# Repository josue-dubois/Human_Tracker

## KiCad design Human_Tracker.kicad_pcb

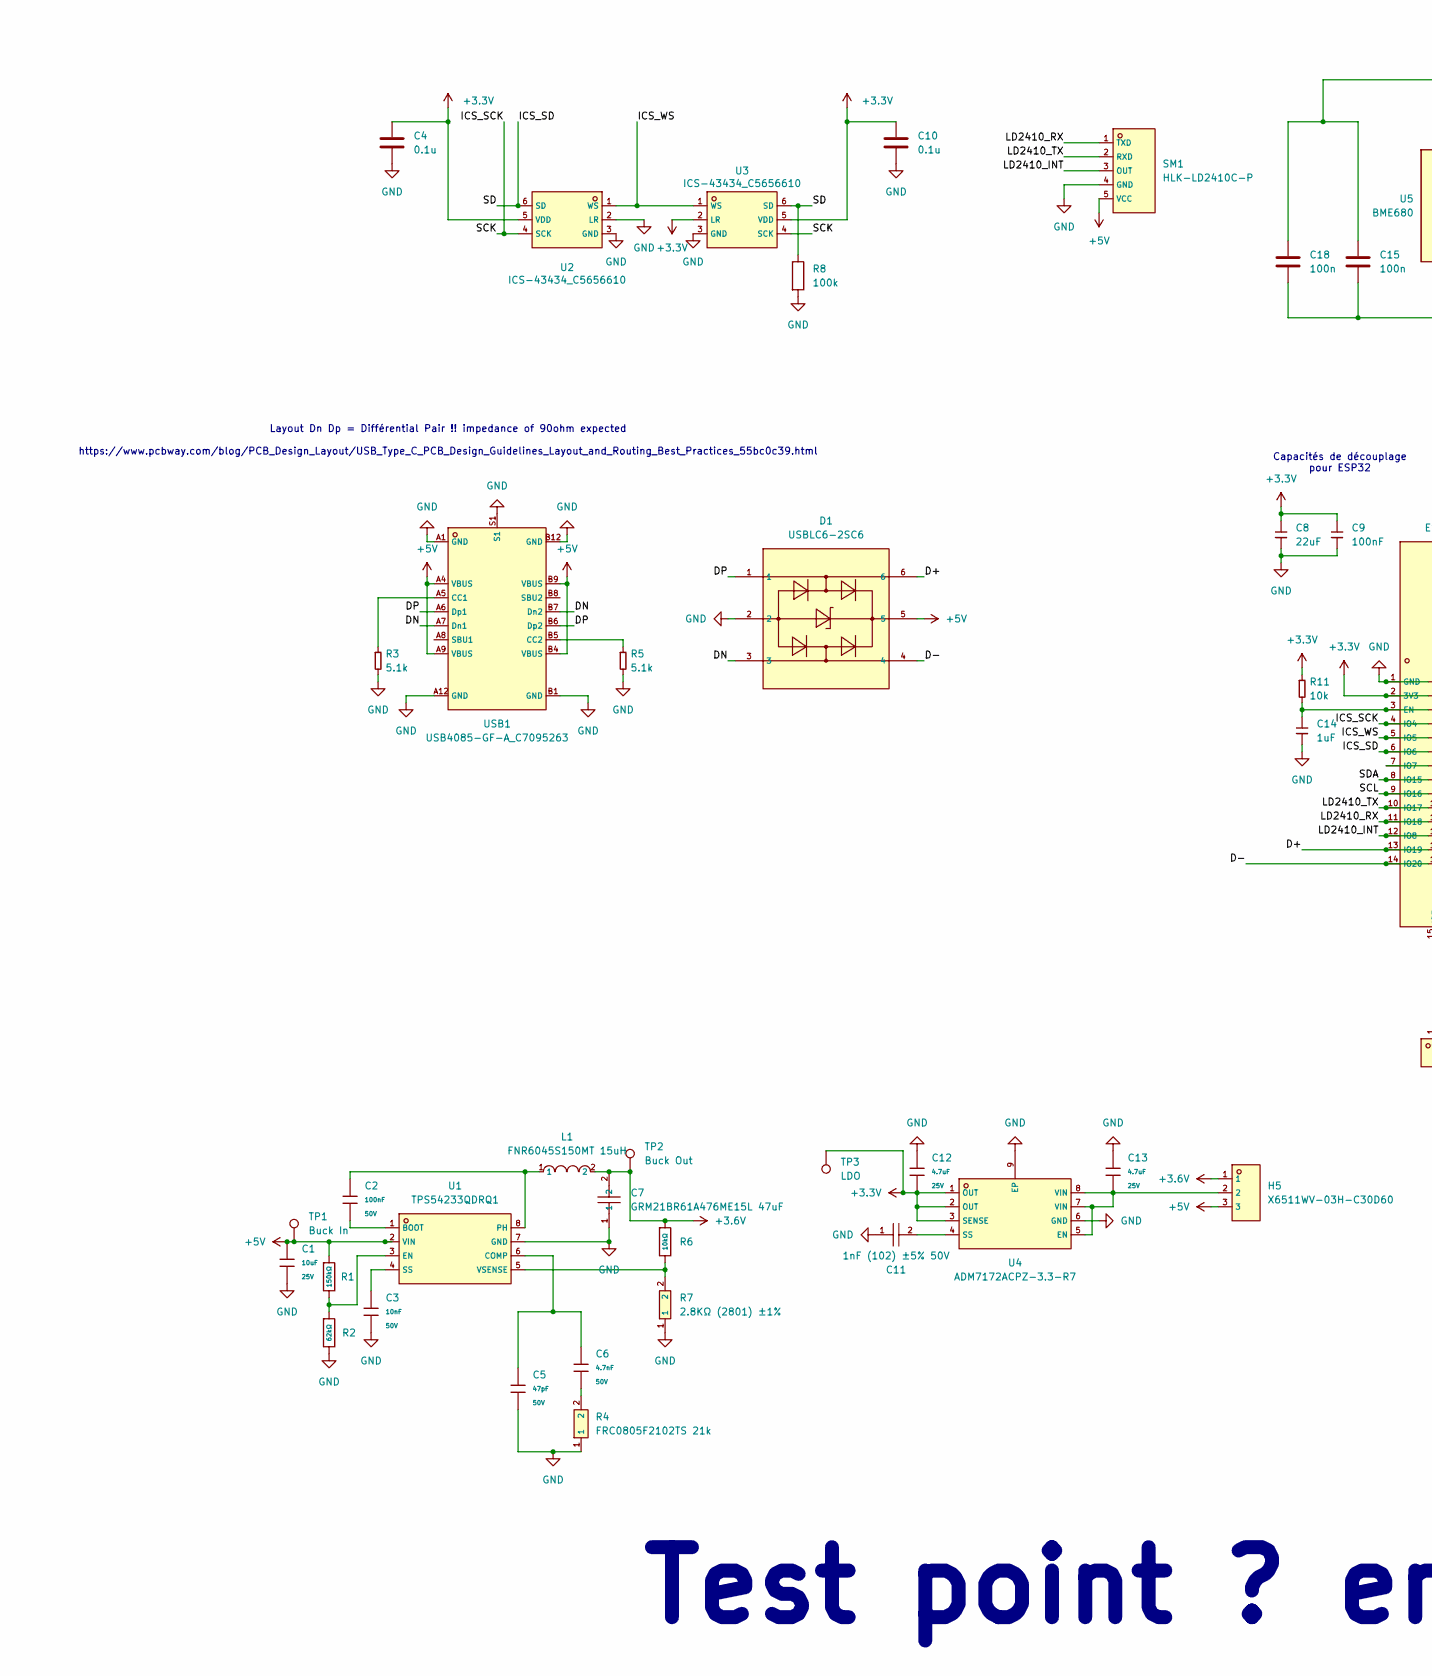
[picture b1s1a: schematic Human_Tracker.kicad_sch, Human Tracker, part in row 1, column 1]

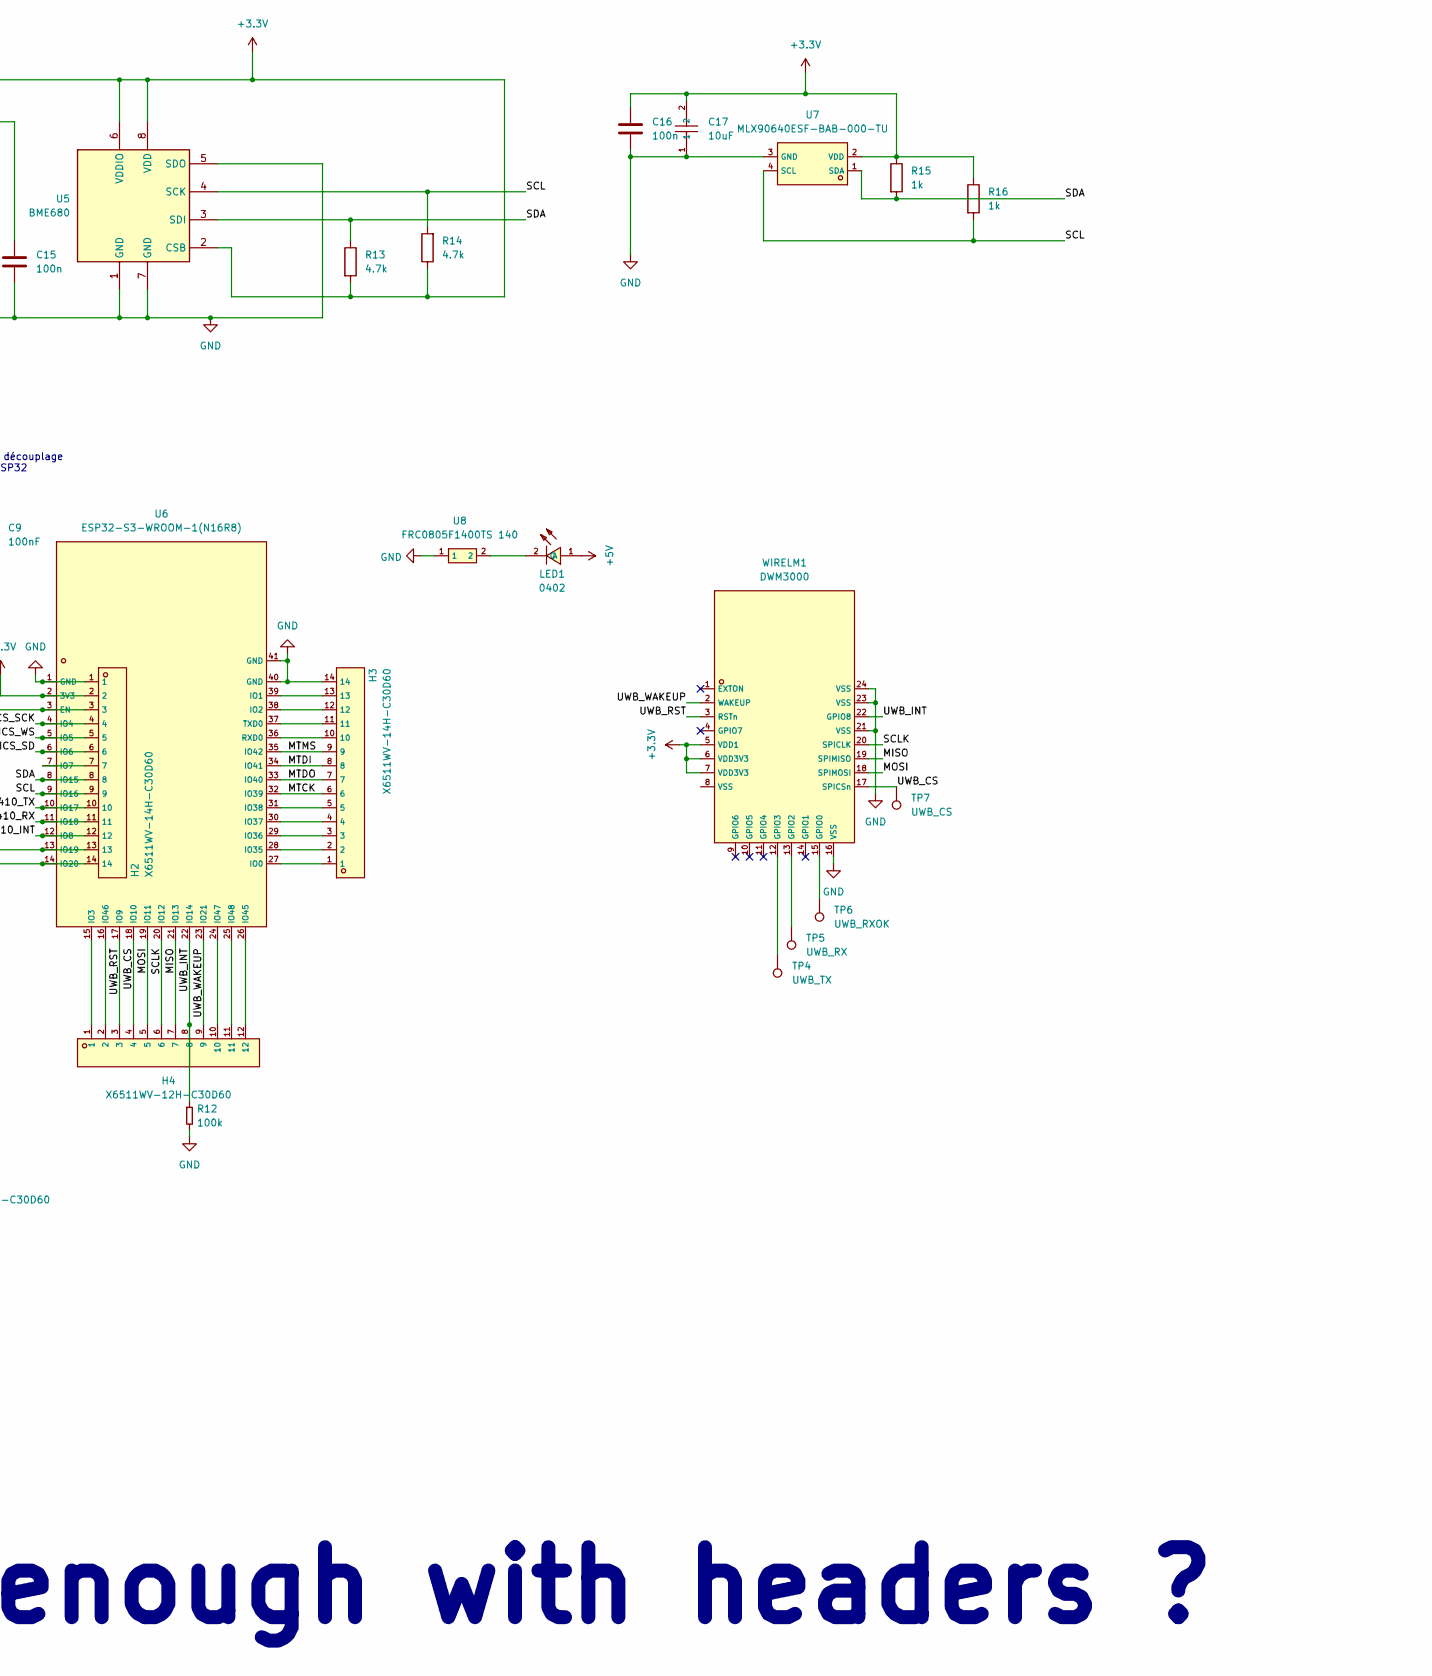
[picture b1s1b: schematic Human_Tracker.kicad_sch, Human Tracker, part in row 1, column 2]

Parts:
C1: 10uF; C1712_C0805; Voltage Rated 25V; Tolerance ±10%; Part CL21A106KAYNNNE; LCSC C15850
C2: 100nF; C1712_C0805; Voltage Rated 50V; Tolerance ±10%; Part CC0805KRX7R9BB104; LCSC C49678
C3: 10nF; C1712_C0805; Voltage Rated 50V; Tolerance ±10%; Part CL21B103KBANNNC; LCSC C1710
C4, C10: 0.1u; C1712_C0805
C5: 47pF; C1712_C0805; Voltage Rated 50V; Tolerance ±5%; Part CL21C470JBANNNC; LCSC C14857
C6: 4.7nF; C1712_C0805; Voltage Rated 50V; Tolerance ±10%; Part 0805B472K500NT; LCSC C1744
C7: GRM21BR61A476ME15L 47uF; C1712_C0805; LCSC C124129
C8: 22uF; C1712_C0805; LCSC C29277
C9: 100nF; C1712_C0805; LCSC C49678
C11: 1nF (102) ±5% 50V; C1712_C0805; LCSC C1791
C12, C13: 4.7uF; C1712_C0805; Voltage Rated 25V; Tolerance ±10%; Part CL21A475KAQNNNE; LCSC C1779
C14: 1uF; C1712_C0805; LCSC C1712
C15, C16, C18: 100n; C1712_C0805
C17: 10uF; C15850_C0805; LCSC C15850
D1: USBLC6-2SC6; C7519_SOT-23-6_L2_9-W1_6-P0_95-LS2_8-BL; LCSC C7519
H2, H3: X6511WV-14H-C30D60; C725946_HDR-TH_14P-P2_54-V-M; LCSC C725946
H4: X6511WV-12H-C30D60; C725944_HDR-TH_12P-P2_54-V-M; LCSC C725944
H5: X6511WV-03H-C30D60; C706875_HDR-TH_3P-P2_54-V-M; LCSC C706875
L1: FNR6045S150MT 15uH; C168078_IND-SMD_L6_0-W6_0_FNR60XXS; LCSC C168078
LED1: 0402; C74338_LED0402-R-RD; LCSC C74338
R1: 150kΩ; C17414_R0805; Overload Voltage (Max) 150V; Tolerance ±1%; Part 0805W8F1503T5E; LCSC C17470
R2: 62kΩ; C17414_R0805; Overload Voltage (Max) 150V; Tolerance ±1%; Part 0805W8F6202T5E; LCSC C17783
R3, R5: 5.1k; C17414_R0805; LCSC C26023
R4: FRC0805F2102TS 21k; C17414_R0805; LCSC C2933366
R6: 10kΩ; C17414_R0805; Overload Voltage (Max) 150V; Tolerance ±1%; Part 0805W8F1002T5E; LCSC C17414
R7: 2.8KΩ (2801) ±1%; C17414_R0805; LCSC C17534
R8, R12: 100k; C17414_R0805; LCSC C25611
R11: 10k; C17414_R0805; LCSC C17414
R13, R14: 4.7k; C17414_R0805
R15, R16: 1k; C17414_R0805
SM1: HLK-LD2410C-P; C19723500_SENSOR-TH_HLK-LD2410C-P; LCSC C19723500
TP1: Buck In; TestPoint_Pad_D2.0mm
TP2: Buck Out; TestPoint_Pad_D2.0mm
TP3: LDO; TestPoint_Pad_D2.0mm
TP4: UWB_TX; TestPoint_Pad_D2.0mm
TP5: UWB_RX; TestPoint_Pad_D2.0mm
TP6: UWB_RXOK; TestPoint_Pad_D2.0mm
TP7: UWB_CS; TestPoint_Pad_D2.0mm
U1: TPS54233QDRQ1; C2865142_SOIC-8_L4_9-W3_9-P1_27-LS6_0-BL; LCSC C2865142
U2, U3: ICS-43434_C5656610; C5656610_MIC-SMD_6P-L3_5-W2_7-P0_90-BL; LCSC C5656610
U4: ADM7172ACPZ-3.3-R7; C514342_DFN-8_L3_0-W3_0-P0_50-BL-EP; LCSC C514342
U5: BME680; Bosch_LGA-8_3x3mm_P0.8mm_ClockwisePinNumbering
U6: ESP32-S3-WROOM-1(N16R8); C2913202_WIRELM-SMD_ESP32-S3-WROOM-1; LCSC C2913202
U7: MLX90640ESF-BAB-000-TU; C488251_TO-39-4_MLX90640ESF-BAB-000-TU; LCSC C488251
U8: FRC0805F1400TS 140; C2930166_R0805; LCSC C2930166
USB1: USB4085-GF-A_C7095263; C7095263_USC-C-SMD_USB4085-GF-A; LCSC C7095263
WIRELM1: DWM3000; C3028890_WIRELM-SMD_DWM3000; LCSC C3028890

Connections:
+3.3V: C4.1, C8.1, C9.1, C10.1, C12.2, C15.1, C16.1, C17.2, C18.1, H2.2, R11.1, R13.2, R14.1, R15.1, R16.1, TP3.1 (1_1), U2.5 (VDD), U3.2 (LR), U3.5 (VDD), U4.1 (OUT), U4.2 (OUT), U4.3 (SENSE), U5.2 (CSB), U5.6 (VDDIO), U5.8 (VDD), U6.2 (3V3), U7.2 (VDD), WIRELM1.5 (VDD1), WIRELM1.6 (VDD3V3), WIRELM1.7 (VDD3V3)
+3.6V: C7.2, H5.1, L1.2, R6.1, TP2.1 (1_1)
+5V: C1.1, D1.5, H5.3, LED1.1 (A), R1.1, SM1.5 (VCC), TP1.1 (1_1), U1.2 (VIN), USB1.A4 (VBUS), USB1.A9 (VBUS), USB1.B4 (VBUS), USB1.B9 (VBUS)
/D+: D1.6, H2.13, U6.13 (IO19)
/D-: D1.4, H2.14, U6.14 (IO20)
/DN: D1.3, USB1.A7 (Dn1), USB1.B7 (Dn2)
/DP: D1.1, USB1.A6 (Dp1), USB1.B6 (Dp2)
/ICS_SCK: H2.4, U2.4 (SCK), U3.4 (SCK), U6.4 (IO4)
/ICS_SD: H2.6, R8.1, U2.6 (SD), U3.6 (SD), U6.6 (IO6)
/ICS_WS: H2.5, U2.1 (WS), U3.1 (WS), U6.5 (IO5)
/LD2410_INT: H2.12, SM1.3 (OUT), U6.12 (IO8)
/LD2410_RX: H2.11, SM1.1 (TXD), U6.11 (IO18)
/LD2410_TX: H2.10, SM1.2 (RXD), U6.10 (IO17)
/MISO: H4.7, U6.21 (IO13), WIRELM1.19 (SPIMISO)
/MOSI: H4.5, U6.19 (IO11), WIRELM1.18 (SPIMOSI)
/MTCK: H3.6, U6.32 (IO39)
/MTDI: H3.8, U6.34 (IO41)
/MTDO: H3.7, U6.33 (IO40)
/MTMS: H3.9, U6.35 (IO42)
/SCL: H2.9, R14.2, R16.2, U5.4 (SCK), U6.9 (IO16), U7.4 (SCL)
/SCLK: H4.6, U6.20 (IO12), WIRELM1.20 (SPICLK)
/SDA: H2.8, R13.1, R15.2, U5.3 (SDI), U6.8 (IO15), U7.1 (SDA)
/UWB_CS: H4.4, TP7.1 (1_1), U6.18 (IO10), WIRELM1.17 (SPICSn)
/UWB_INT: H4.8, R12.1, U6.22 (IO14), WIRELM1.22 (GPIO8)
/UWB_RST: H4.3, U6.17 (IO9), WIRELM1.3 (RSTn)
/UWB_WAKEUP: H4.9, U6.23 (IO21), WIRELM1.2 (WAKEUP)
GND: C1.2, C3.2, C4.2, C5.2, C7.1, C8.2, C9.2, C10.2, C11.1, C12.1, C13.1, C14.2, C15.2, C16.2, C17.1, C18.2, D1.2, H2.1, H3.14, R2.2, R3.2, R4.1, R5.2, R7.1, R8.2, R12.2, SM1.4 (GND), U1.7 (GND), U2.2 (LR), U2.3 (GND), U3.3 (GND), U4.6 (GND), U4.9 (EP), U5.1 (GND), U5.5 (SDO), U5.7 (GND), U6.1 (GND), U6.40 (GND), U6.41 (GND), U7.3 (GND), U8.1, USB1.A1 (GND), USB1.A12 (GND), USB1.B1 (GND), USB1.B12 (GND), USB1.S1, WIRELM1.16 (VSS), WIRELM1.21 (VSS), WIRELM1.23 (VSS), WIRELM1.24 (VSS)
unnamed: C6.2, R4.2
unnamed: LED1.2 (C), U8.2
unnamed: C2.2, U1.1 (BOOT)
unnamed: C5.1, C6.1, U1.6 (COMP)
unnamed: R1.2, R2.1, U1.3 (EN)
unnamed: C2.1, L1.1, U1.8 (PH)
unnamed: C3.1, U1.4 (SS)
unnamed: R6.2, R7.2, U1.5 (VSENSE)
unnamed: C13.2, H5.2, U4.5 (EN), U4.7 (VIN), U4.8 (VIN)
unnamed: C11.2, U4.4 (SS)
unnamed: C14.1, H2.3, R11.2, U6.3 (EN)
unnamed: H3.1, U6.27 (IO0)
unnamed: H3.13, U6.39 (IO1)
unnamed: H3.12, U6.38 (IO2)
unnamed: H4.1, U6.15 (IO3)
unnamed: H2.7, U6.7 (IO7)
unnamed: H3.2, U6.28 (IO35)
unnamed: H3.3, U6.29 (IO36)
unnamed: H3.4, U6.30 (IO37)
unnamed: H3.5, U6.31 (IO38)
unnamed: H4.12, U6.26 (IO45)
unnamed: H4.2, U6.16 (IO46)
unnamed: H4.10, U6.24 (IO47)
unnamed: H4.11, U6.25 (IO48)
unnamed: H3.10, U6.36 (RXD0)
unnamed: H3.11, U6.37 (TXD0)
unnamed: R3.1, USB1.A5 (CC1)
unnamed: R5.1, USB1.B5 (CC2)
unnamed: TP6.1 (1_1), WIRELM1.15 (GPIO0)
unnamed: TP5.1 (1_1), WIRELM1.13 (GPIO2)
unnamed: TP4.1 (1_1), WIRELM1.12 (GPIO3)

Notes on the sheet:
Test point ? enough with headers ?
Capacités de découplage pour ESP32
Layout Dn Dp = Différential Pair !! impedance of 90ohm expected https://www.pcbway.com/blog/PCB_Design_Layout/USB_Type_C_PCB_Design_Guidelines_Layout_and_Routing_Best_Practices_55bc0c39.html

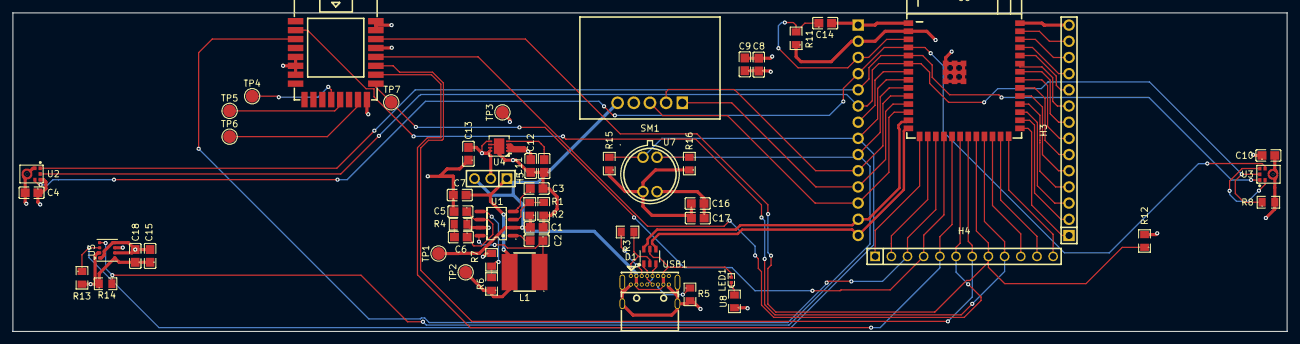
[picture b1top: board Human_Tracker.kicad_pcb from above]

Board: 4 copper layers, 200.0 x 50.0 mm, 57 parts (1 on the bottom side), 58 nets.
